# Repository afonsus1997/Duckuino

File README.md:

# 

### The truly open-source atmega32u4 ducky clone (V2.0)

## Info

Enter the duckuino, the fully open-source USB rubberducky clone based on the atmega32u4

## BOM

## PINMAP
PINMAP of the ATMEGA32u4

| PIN | ALT FUNCTION | OLED | Thumbwheel | LEDs | DIP Sw's |       SD       |
|:---:|:------------:|:----:|:----------:|:----:|:--------:|:--------------:|
| D2  | SDA          |  SDA |      -     |   -  |     -    |        -       |
| D3  | SCL          |  SCL |      -     |   -  |     -    |        -       |
| D4  | A6           |   -  |      -     |   -  |     -    | CD/DAT3 (!CS!) |
| D5  | -            |   -  |      -     |   -  |     4    |        -       |
| D6  | A7           |   -  |      -     | LED1 |     -    |        -       |
| D7  | -            |   -  |      -     | LED2 |     -    |        -       |
| D8  | A8           |   -  |   Center   |   -  |     -    |        -       |
| D9  | A9           |   -  |      -     |   -  | 1 (Boot) |        -       |
| D10 | A10          |   -  |      -     |   -  |     2    |        -       |
| D11 | -            |   -  |    Right   |   -  |     -    |        -       |
| D12 | -            |   -  |    Left    |   -  |     -    |        -       |
| D13 | -            |   -  |      -     |   -  |     3    |        -       |
| D14 | -            |   -  |      -     |   -  |     -    |    DAT0 (D0)   |
| D15 | -            |   -  |      -     |   -  |     -    |   CLK (SCLK)   |
| D16 | -            |   -  |      -     |   -  |     -    |    CMD (DI)    |

## Renders & Pictures

### V2.0 Altium Renders

## Old Version Renders & Pictures

### V0.1 Photos

### V0.1 Renders

### V0.1 Eagle Renders

### V0.1 PCB pictures

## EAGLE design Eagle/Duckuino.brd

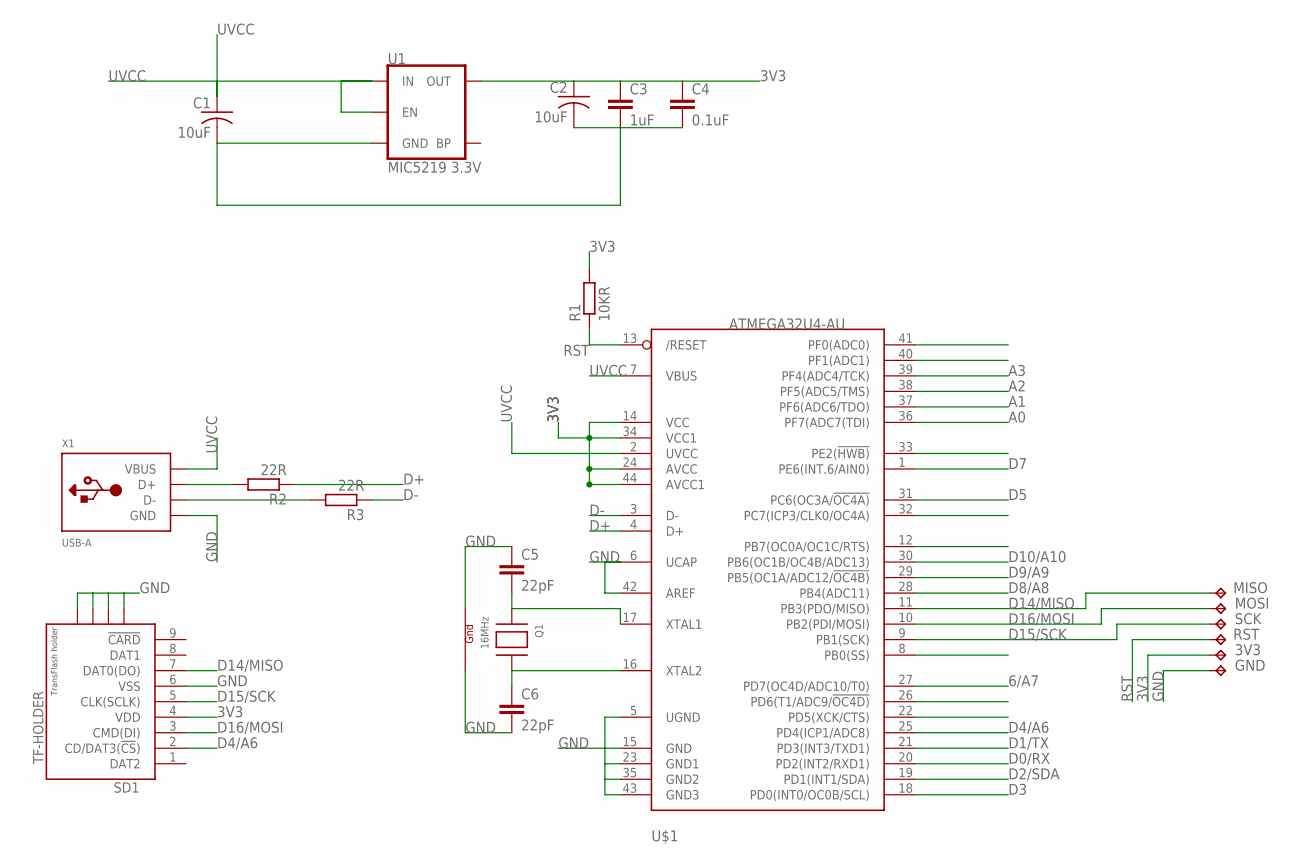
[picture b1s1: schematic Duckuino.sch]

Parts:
3V3: TPTP11R; TP11R
C1, C2: 10uF; C0603
C3: 1uF; C0603
C4: 0.1uF; C0603
C5, C6: 22pF; C0603
GND: TPTP11R; TP11R
MISO: TPTP11R; TP11R
MOSI: TPTP11R; TP11R
Q1: 16MHz; NX3225
R1: 10KR; R0603
R2, R3: 22R; R0603
RST: TPTP11R; TP11R
SCK: TPTP11R; TP11R
SD1: TF-HOLDER; TF-PULL
U1: MIC5219 3.3V; SOT23-5
U$1: ATMEGA32U4-AU; TQFP44
X1: USB-A; MOLEX_480371000

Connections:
3V3: 3V3.TP, C2.1, C3.1, C4.1, R1.2, SD1.4 (VDD), U1.5 (OUT), U$1.14 (VCC), U$1.24 (AVCC), U$1.34 (VCC1), U$1.44 (AVCC1)
6/A7: U$1.27 (PD7(OC4D/ADC10/T0))
A0: U$1.36 (PF7(ADC7(TDI))
A1: U$1.37 (PF6(ADC6/TDO))
A2: U$1.38 (PF5(ADC5/TMS))
A3: U$1.39 (PF4(ADC4/TCK))
D0/RX: U$1.20 (PD2(INT2/RXD1))
D1/TX: U$1.21 (PD3(INT3/TXD1))
D2/SDA: U$1.19 (PD1(INT1/SDA))
D3: U$1.18 (PD0(INT0/OC0B/SCL))
D4/A6: SD1.2 (CD/DAT3(!CS!)), U$1.25 (PD4(ICP1/ADC8))
D5: U$1.31 (PC6(OC3A/!OC4A))
D7: U$1.1 (PE6(INT.6/AIN0))
D8/A8: U$1.28 (PB4(ADC11))
D9/A9: U$1.29 (PB5(OC1A/ADC12/!OC4B))
D10/A10: U$1.30 (PB6(OC1B/OC4B/ADC13))
D14/MISO: MISO.TP, SD1.7 (DAT0(DO)), U$1.11 (PB3(PDO/MISO))
D15/SCK: SCK.TP, SD1.5 (CLK(SCLK)), U$1.9 (PB1(SCK))
D16/MOSI: MOSI.TP, SD1.3 (CMD(DI)), U$1.10 (PB2(PDI/MOSI))
D+: R2.1, U$1.4 (D+)
D-: R3.1, U$1.3 (D-)
GND: C1.2, C2.2, C3.2, C4.2, C5.1, C6.2, GND.TP, Q1.2 (G2), Q1.4 (G1), SD1.6 (VSS), SD1.S1, SD1.S2, SD1.S3, SD1.S4, U1.2 (GND), U$1.5 (UGND), U$1.6 (UCAP), U$1.15 (GND), U$1.23 (GND1), U$1.35 (GND2), U$1.42 (AREF), U$1.43 (GND3), X1.4 (GND)
unnamed: R2.2, X1.3 (D+)
unnamed: R3.2, X1.2 (D-)
unnamed: C6.1, Q1.3 (X2), U$1.16 (XTAL2)
unnamed: C5.2, Q1.1 (X1), U$1.17 (XTAL1)
RST: R1.1, RST.TP, U$1.13 (/RESET)
UVCC: C1.1, U1.1 (IN), U1.3 (EN), U$1.2 (UVCC), U$1.7 (VBUS), X1.1 (VBUS)

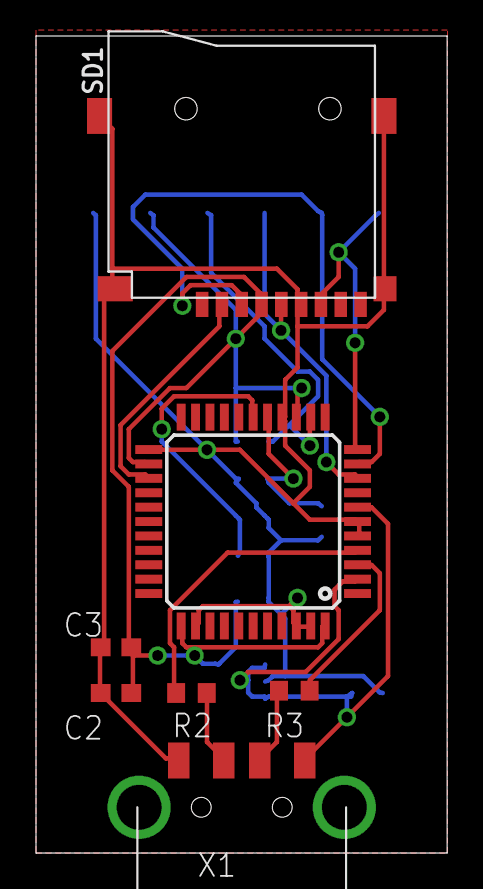
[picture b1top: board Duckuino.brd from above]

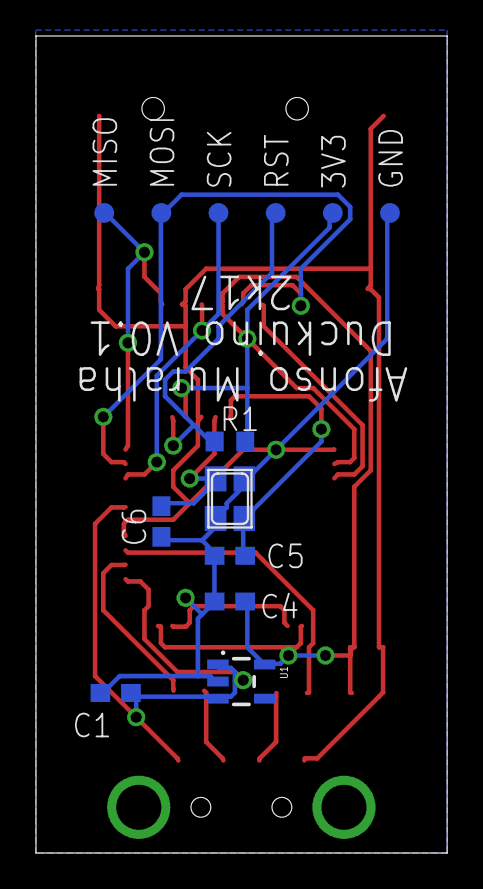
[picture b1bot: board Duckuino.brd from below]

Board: 2 copper layers, 22.8 x 45.4 mm, 20 parts (13 on the bottom side), 14 nets.

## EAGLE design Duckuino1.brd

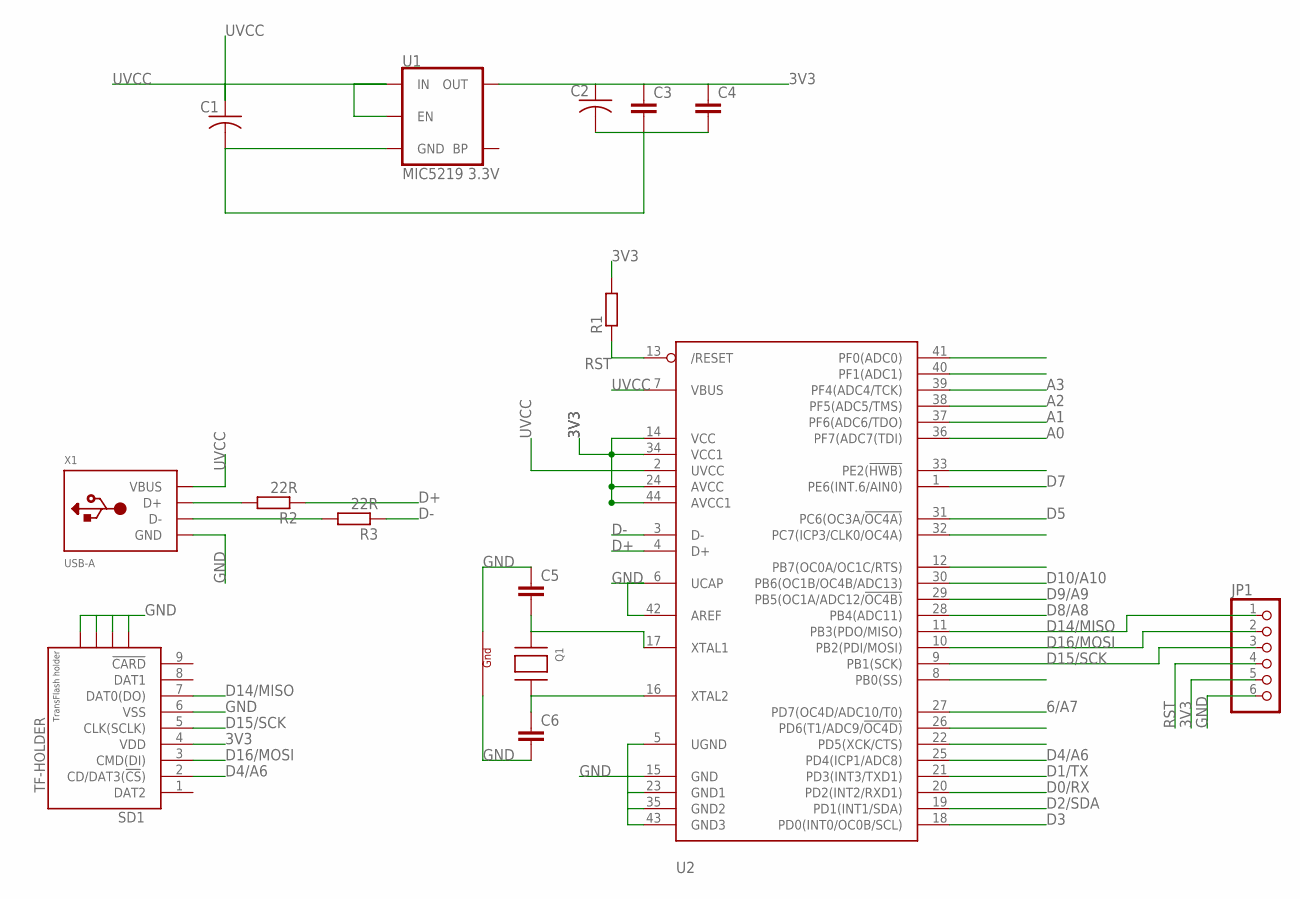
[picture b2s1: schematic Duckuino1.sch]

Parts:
C1, C2: C-USC0603; C0603
C3, C4, C5, C6: C-EUC0603; C0603
JP1: PINHD-1X6; 1X06
Q1: XTAL-4-3225; NX3225
R1: RR0603; R0603
R2, R3: 22R; R0603
SD1: TF-HOLDER; TF-PULL
U1: MIC5219 3.3V; SOT23-5
U2: ATMEGA32U4-AU; TQFP44
X1: USB-A; MOLEX_480371000

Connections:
3V3: C2.1, C3.1, C4.1, JP1.5, R1.2, SD1.4 (VDD), U1.5 (OUT), U2.14 (VCC), U2.24 (AVCC), U2.34 (VCC1), U2.44 (AVCC1)
6/A7: U2.27 (PD7(OC4D/ADC10/T0))
A0: U2.36 (PF7(ADC7(TDI))
A1: U2.37 (PF6(ADC6/TDO))
A2: U2.38 (PF5(ADC5/TMS))
A3: U2.39 (PF4(ADC4/TCK))
D0/RX: U2.20 (PD2(INT2/RXD1))
D1/TX: U2.21 (PD3(INT3/TXD1))
D2/SDA: U2.19 (PD1(INT1/SDA))
D3: U2.18 (PD0(INT0/OC0B/SCL))
D4/A6: SD1.2 (CD/DAT3(!CS!)), U2.25 (PD4(ICP1/ADC8))
D5: U2.31 (PC6(OC3A/!OC4A))
D7: U2.1 (PE6(INT.6/AIN0))
D8/A8: U2.28 (PB4(ADC11))
D9/A9: U2.29 (PB5(OC1A/ADC12/!OC4B))
D10/A10: U2.30 (PB6(OC1B/OC4B/ADC13))
D14/MISO: JP1.1, SD1.7 (DAT0(DO)), U2.11 (PB3(PDO/MISO))
D15/SCK: JP1.3, SD1.5 (CLK(SCLK)), U2.9 (PB1(SCK))
D16/MOSI: JP1.2, SD1.3 (CMD(DI)), U2.10 (PB2(PDI/MOSI))
D+: R2.1, U2.4 (D+)
D-: R3.1, U2.3 (D-)
GND: C1.2, C2.2, C3.2, C4.2, C5.1, C6.2, JP1.6, Q1.2 (G2), Q1.4 (G1), SD1.6 (VSS), SD1.S1, SD1.S2, SD1.S3, SD1.S4, U1.2 (GND), U2.5 (UGND), U2.6 (UCAP), U2.15 (GND), U2.23 (GND1), U2.35 (GND2), U2.42 (AREF), U2.43 (GND3), X1.4 (GND)
unnamed: R2.2, X1.3 (D+)
unnamed: R3.2, X1.2 (D-)
unnamed: C6.1, Q1.3 (X2), U2.16 (XTAL2)
unnamed: C5.2, Q1.1 (X1), U2.17 (XTAL1)
RST: JP1.4, R1.1, U2.13 (/RESET)
UVCC: C1.1, U1.1 (IN), U1.3 (EN), U2.2 (UVCC), U2.7 (VBUS), X1.1 (VBUS)

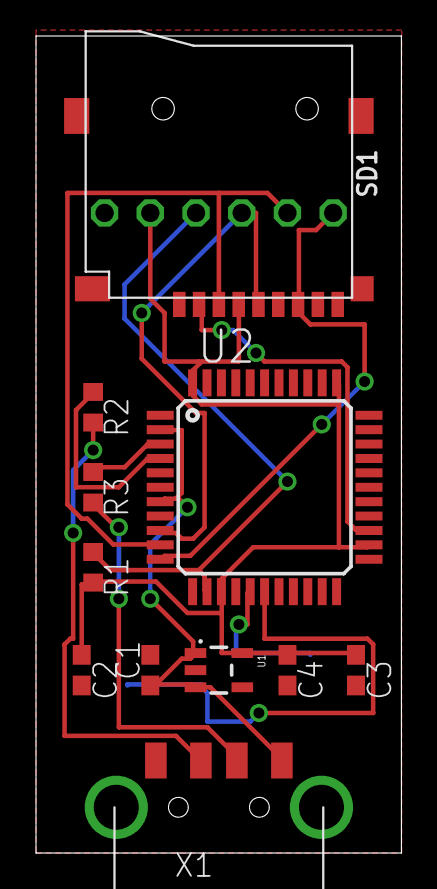
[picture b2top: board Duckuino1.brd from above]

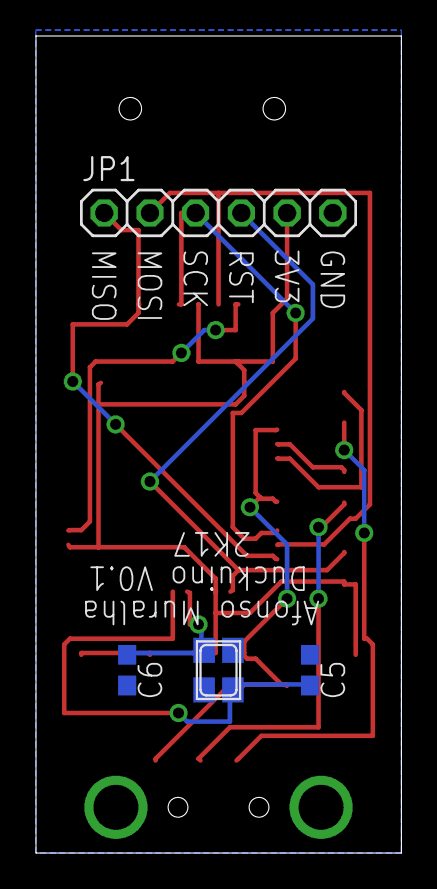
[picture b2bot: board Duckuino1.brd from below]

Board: 2 copper layers, 20.3 x 45.4 mm, 15 parts (4 on the bottom side), 14 nets.

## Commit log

2017-02-16 Added main files for version 0.1
2017-02-16 created separate branches for versions
2017-02-16 created sparate branches for versions
2017-02-16 Added log to readme
2017-02-16 fixed readme
2017-02-16 Added pictures and renders and edited README.md
2017-02-16 more pictures
2017-02-16 Added renders and edited README.md
2017-02-16 more info on readme
2017-02-16 addedd eagle renders and boms
2017-02-16 again
2017-02-16 test
2017-03-10 Seprate Eagle folder in order to add altium files
2017-03-10 Added main Altium files and Libraries
2017-03-10 Started working on schematics and edited some libraries
2017-03-10 edited readme
2017-03-10 updated schematic and created more libs
2017-03-15 Completed circuit and added pinmap to readme
2017-03-15 fix readme?
2017-03-15 trying to fix markdown
2017-03-15 Fixed??
2017-03-16 Started testing pcb layout and added soldered pictures
2017-03-16 tried to fix photos
2017-03-20 random tests
2017-03-22 added the pinout of the crystal and edited some stuff i guess
2018-04-15 redoing schematics, added new libs
2018-04-16 Nesting
2018-04-16 started routing, added lcd model
2018-04-18 finished routing, added 3d models
2018-04-18 replaced pic
2018-04-20 sent to fab
2018-04-22 New custom bootloader
2018-04-22 new readme, added pinouts
2018-04-25 development on formware
2018-04-25 added logo to splashscreen
2018-04-25 changed things around, moved to lighter libs
2018-04-25 fixed readme -_-;
2018-04-25 -_-;
2018-05-01 added labels pdf
2018-05-14 fixed schematic, started routing
2018-05-24 did routing
2018-06-09 new xtal
2018-06-12 new silkscreen
2018-06-16 sent new version to fab, testing white soldermask
2018-07-13 firmware menu system on the works
2018-07-14 more wwork done on menus
2018-07-24 delay finaly works
2018-08-27 basic script works!
2018-08-27 this code is a mess! but hey! it works!
2018-08-29 word done on the code, still a mess
2018-09-01 code will remain forever a mess
2019-03-12 Code still a mess, added special splash screen for pixels camp v3

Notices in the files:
parts and their libraries:
SparkFun-IC-Power: Licensing: Creative Commons ShareAlike 4.0 International - https://creativecommons.org/licenses/by-sa/4.0
